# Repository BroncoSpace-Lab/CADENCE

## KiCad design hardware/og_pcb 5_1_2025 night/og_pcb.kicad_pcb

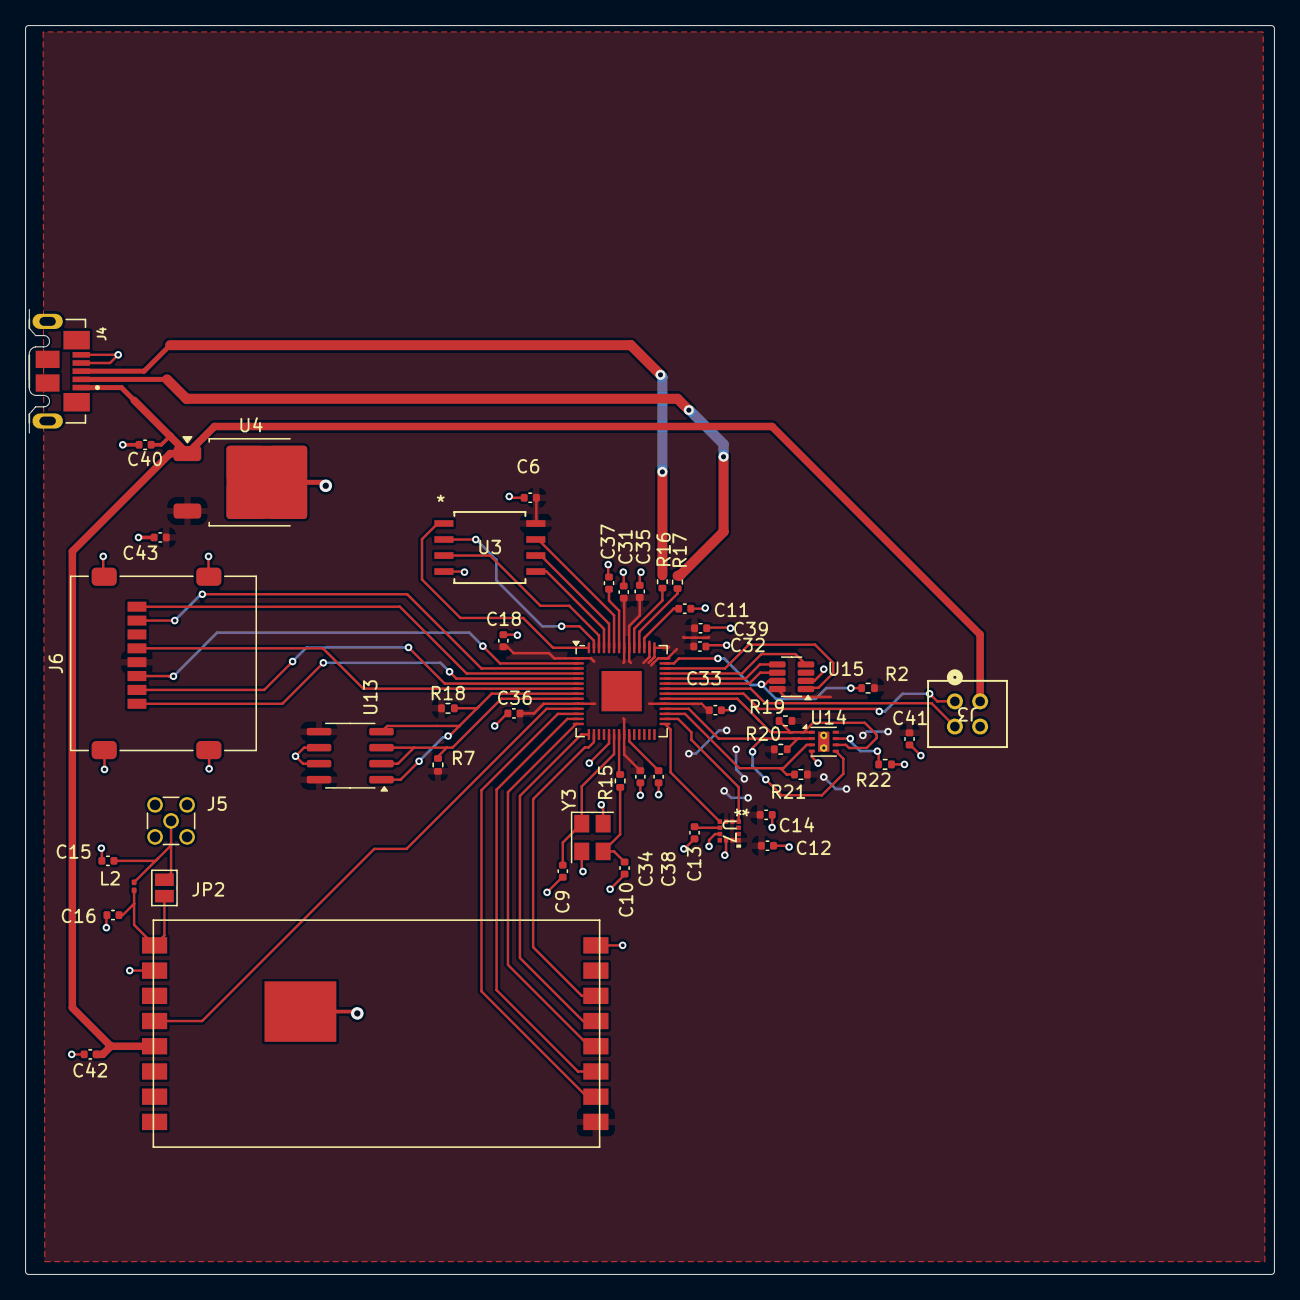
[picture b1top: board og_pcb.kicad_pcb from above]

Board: 2 copper layers, 99.1 x 99.1 mm, 48 parts (0 on the bottom side), 47 nets.

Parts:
C6, C18, C31, C32, C33, C34, C35, C36, C37, C38, C42: 100n; C_0402_1005Metric
C9, C10: 15p; C_0402_1005Metric
C11, C39: 1u; C_0402_1005Metric
C12, C14: 100nF; C_0402_1005Metric
C13: 220nF; C_0402_1005Metric
C15, C16: DNP; C_0402_1005Metric
C40, C43: 10u; C_0402_1005Metric
C41: 0.01uF; C_0402_1005Metric
J3: Conn_01x04_Pin; CON4_2X2_UF_DF11_HIR
J4: USB_B_Micro; microUSB
J5: Conn_Coaxial; MMCX_Molex_73415-1471_Vertical
J6: Micro_SD_Card; microSD_HC_Molex_47219-2001
JP2: SolderJumper_2_Open; SolderJumper-2_P1.3mm_Open_Pad1.0x1.5mm
L2: DNP; L_0201_0603Metric
R2, R7, R18: 10k; R_0402_1005Metric
R15: 1k; R_0402_1005Metric
R16, R17: 27; R_0402_1005Metric
R19, R20, R21, R22: 5k; R_0402_1005Metric
U3: W25Q128JVS; SOIC_208MIL_WIN
U4: BD33FC0FP; TO-252-2
U7: LSM303AGRTR; SON_03AGRTR_STM-L
U12: RP2040; QFN-56-1EP_7x7mm_P0.4mm_EP3.2x3.2mm
U13: INA219AxD; SOIC-8_3.9x4.9mm_P1.27mm
U14: TMP1075DSG; WSON-8-1EP_2x2mm_P0.5mm_EP0.9x1.6mm_ThermalVias
U15: MAX6369; SOT-23-8
U16: RFM98PW
Y3: ABM8-272-T3; Crystal_SMD_3225-4Pin_3.2x2.5mm

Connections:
+1V1: C11.1, C37.1, C38.1, U12.23 (DVDD), U12.45 (VREG_VOUT), U12.50 (DVDD)
/RP2040 MCU/Crystal In: C9.1, U12.20 (XIN), Y3.1
/RP2040 MCU/Crystal Out: R15.1, U12.21 (XOUT)
/RP2040 MCU/QSPI_SCLK: U3.6 (CLK), U12.52 (QSPI_SCLK)
/RP2040 MCU/QSPI_SD0: U3.5 (DI(IO0)), U12.53 (QSPI_SD0)
/RP2040 MCU/QSPI_SD1: U3.2 (DO(IO1)), U12.55 (QSPI_SD1)
/RP2040 MCU/QSPI_SD2: U3.3 (IO2), U12.54 (QSPI_SD2)
/RP2040 MCU/QSPI_SD3: U3.7 (IO3), U12.51 (QSPI_SD3)
/RP2040 MCU/QSPI_SS: U3.1 (~CS), U12.56 (QSPI_SS)
Cosmic1 SDA: J3.1, U12.35 (GPIO23)
Cosmic2 SCL: J3.2, U12.36 (GPIO24)
Cosmic Ground: C6.2, C9.2, C10.2, C11.2, C12.2, C13.2, C14.2, C15.2, C16.2, C18.2, C31.2, C32.2, C33.2, C34.2, C35.2, C36.2, C37.2, C38.2, C39.2, C40.2, C41.1, C42.1, C43.2, J3.4, J4.4 (ID), J4.5 (GND), J5.2 (Ext), J6.6 (VSS), J6.9 (SHIELD), R22.2, U3.4 (GND), U4.2 (GND), U7.6 (GND), U7.8 (GND), U12.19 (TESTEN), U12.57 (GND), U13.6 (GND), U13.7 (IN-), U14.4 (GND), U14.9 (EP), U15.2 (GND), U16.2 (GND), U16.16 (GND), U16.17 (GND), Y3.2, Y3.4
Cosmic Power: C40.1, C42.2, J3.3, J4.1 (VBUS), U4.1 (VCC), U16.5 (VCC(5V))
IMU SCL/SPC: U7.1 (SCL/SPC), U12.30 (GPIO19)
IMU SDA/SDI/SCO: U7.4 (SDA/SDI/SCO), U12.29 (GPIO18)
MicroSD CMD: J6.3 (CMD), U12.2 (GPIO0)
MicroSD Clock: J6.5 (CLK), U12.7 (GPIO5)
MicroSD DAT0: J6.7 (DAT0), U12.3 (GPIO1)
MicroSD DAT1: J6.8 (DAT1), U12.4 (GPIO2)
MicroSD DAT2: J6.1 (DAT2), U12.5 (GPIO3)
MicroSD DAT3: J6.2 (DAT3/CD), U12.6 (GPIO4)
unnamed: C10.1, R15.2, Y3.3
unnamed: C15.1, J5.1 (In), JP2.1 (A), L2.1
unnamed: C16.1, JP2.2 (B), L2.2, U16.1 (ANT)
unnamed: C13.1, U7.5 (C1)
unnamed: R17.2, U12.46 (USB_DM)
unnamed: R16.2, U12.47 (USB_DP)
unnamed: R22.1, U14.7 (A0)
Power Monitor SCL: R18.2, U12.8 (GPIO6), U13.1 (A1), U13.4 (SCL)
Power Monitor SDA: R7.2, U12.9 (GPIO7), U13.2 (A0), U13.3 (SDA)
RF DIO4: U12.11 (GPIO8), U16.4 (DI/O4)
RF MISO: U12.12 (GPIO9), U16.10 (MISO)
RF MOSI: U12.13 (GPIO10), U16.11 (MOSI)
RF NSS: U12.15 (GPIO12), U16.13 (NSS)
RF Reset: U12.16 (GPIO13), U16.14 (RESET)
RF SCK: U12.14 (GPIO11), U16.12 (SCK)
SET0: U12.39 (GPIO27_ADC1), U15.4 (SET0)
SET1: U12.38 (GPIO26_ADC0), U15.5 (SET1)
SET2: U12.37 (GPIO25), U15.6 (SET2)
Temp Alert: R21.1, U12.31 (GPIO20), U14.3 (ALERT)
Temp SCL: R20.1, U12.32 (GPIO21), U14.2 (SCL), U14.5 (A2)
Temp SDA: R19.1, U12.34 (GPIO22), U14.1 (SDA), U14.6 (A1)
USB_DM: J4.2 (D-), R17.1
USB_DP: J4.3 (D+), R16.1
Voltage Regulator 3.3V Output: C6.1, C12.1, C14.1, C18.1, C31.1, C32.1, C33.1, C34.1, C35.1, C36.1, C39.1, C41.2, C43.1, J6.4 (VDD), R2.1, R7.1, R18.1, R19.2, R20.2, R21.2, U3.8 (VCC), U4.3 (VO), U7.2 (CS_XL), U7.3 (CS_MAG), U7.9 (Vdd), U7.10 (Vdd_I/O), U12.1 (IOVDD), U12.10 (IOVDD), U12.22 (IOVDD), U12.33 (IOVDD), U12.42 (IOVDD), U12.43 (ADC_AVDD), U12.44 (VREG_IN), U12.48 (USB_VDD), U12.49 (IOVDD), U13.5 (VS), U13.8 (IN+), U14.8 (V+), U15.8 (VCC), U16.9 (3.3V)
WDI: U12.40 (GPIO28_ADC2), U15.1 (WDI)
WDO: R2.2, U12.41 (GPIO29_ADC3), U15.7 (~WDO)
